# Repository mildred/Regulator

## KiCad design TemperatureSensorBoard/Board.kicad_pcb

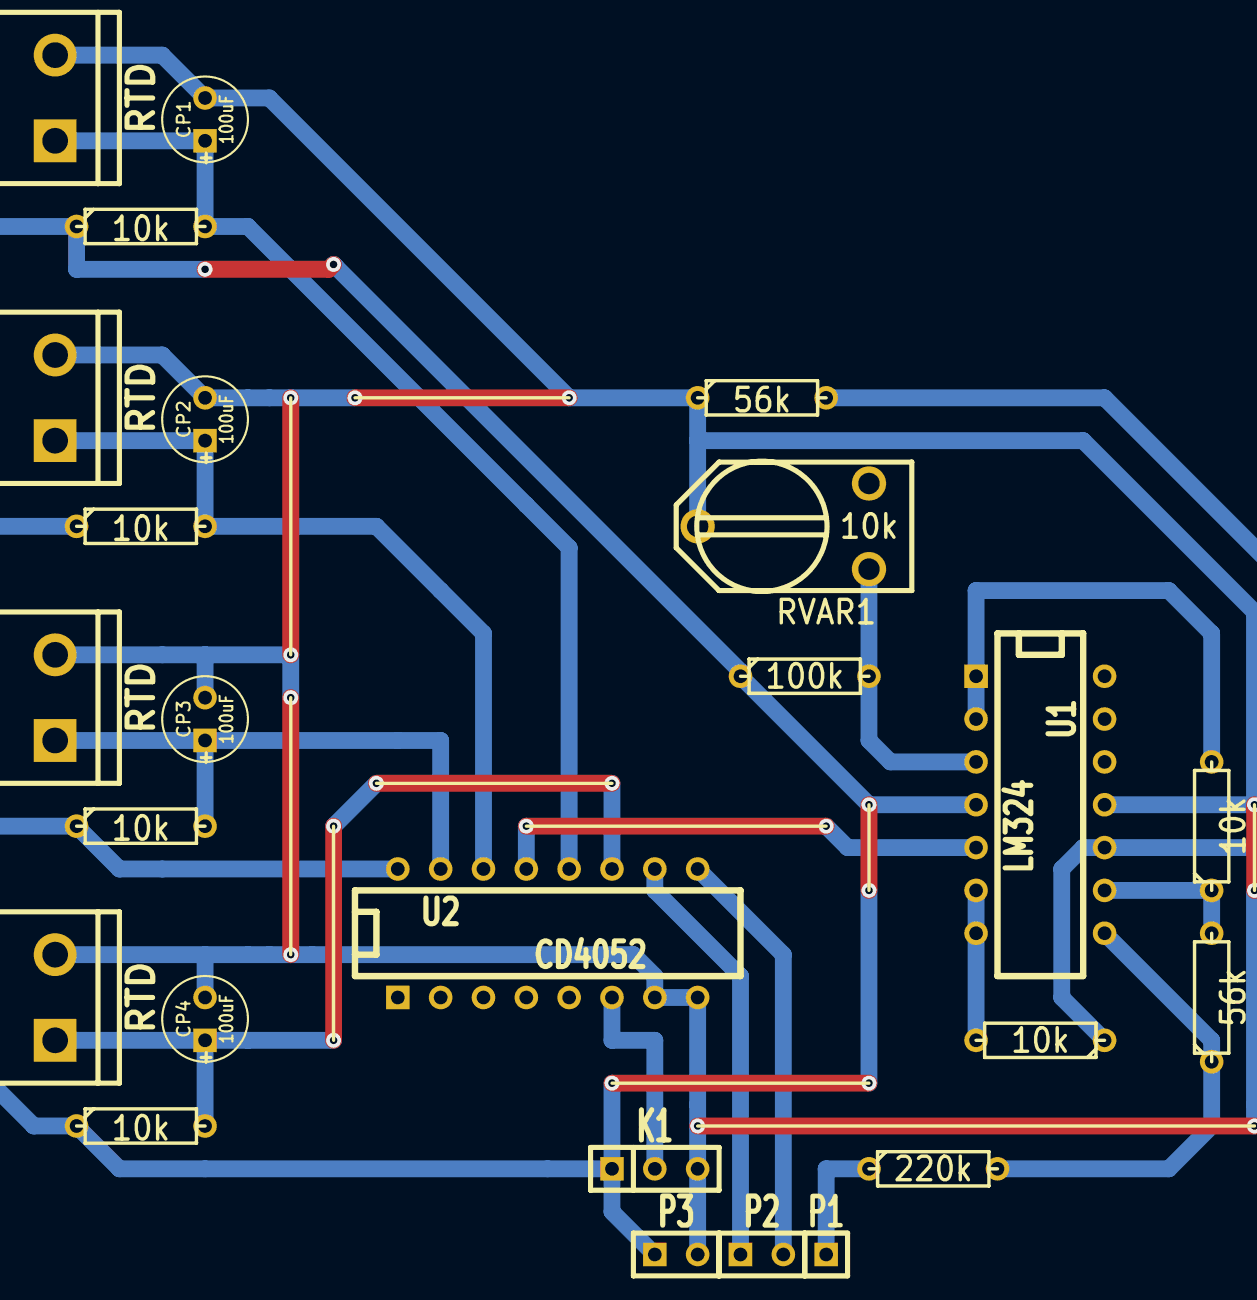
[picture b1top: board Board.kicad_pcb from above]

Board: 2 copper layers, 25 parts (0 on the bottom side), 17 nets.

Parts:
CP1, CP2, CP3, CP4: 100uF; C1V5
K1: CONN_3; SIL-3
P1: CONN_1; SIL-1
P2, P3: CONN_2; SIL-2
PT1000_1, PT1000_2, PT1000_3, PT1000_4: RTD; bornier2
R1, R2, R3, R4, R6, R7: 10k; R3
R5: 100k; R3
R8, R9: 56k; R3
R10: 220k; R3
RVAR1: 10k; RV2X4
U1: LM324; DIP-14__300
U2: CD4052; DIP-16__300

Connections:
GND: CP1.2, CP2.2, CP3.2, CP4.2, K1.3, P3.2, PT1000_1.2, PT1000_2.2, PT1000_3.2, PT1000_4.2, R9.1, RVAR1.2, U1.11, U2.7, U2.8
unnamed: U1.5, U2.13
unnamed: CP4.1, PT1000_4.1, R4.2, U2.11
unnamed: R6.2, U1.1, U1.2
unnamed: R6.1, R8.2, U1.9
unnamed: R7.2, U1.6, U1.7
unnamed: CP3.1, PT1000_3.1, R3.2, U2.15
unnamed: P2.1, U2.10
unnamed: P2.2, U2.9
unnamed: K1.2, U2.6
unnamed: P1.1, R10.1
unnamed: R5.2, RVAR1.1, U1.3
unnamed: R8.1, R10.2, U1.8
unnamed: CP1.1, PT1000_1.1, R1.2, U2.12
unnamed: R7.1, R9.2, U1.10
unnamed: CP2.1, PT1000_2.1, R2.2, U2.14
VCC: K1.1, P3.1, R1.1, R2.1, R3.1, R4.1, R5.1, U1.4, U2.16

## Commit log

2014-03-25 First version of regulator with lots of garbage
2014-03-25 cleanup
2014-09-26 update regulator
2014-10-11 Add support for command line ino tool
2014-10-11 Add board kicad project
2014-10-18 Regulator
2014-10-18 Kicad
2014-10-29 First shipped version
2014-10-29 This is the first version
2014-11-07 Update application
2014-12-02 Use OneWire temperature sensors
2015-01-27 Final version in production for months using digital sensors
2015-09-30 Deleted regulator and renames regulator2 to regulator
2015-09-30 Added version
2015-09-30 Don't stress the hardware when there is no heat
2015-10-01 Improve version display
2015-10-17 Hysteresis on low temperatures
